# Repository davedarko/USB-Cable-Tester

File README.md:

# USB-Cable-Tester
Test your mini, micro and A-A cables with this little device! 

Infos: https://hackaday.io/project/6858-usb-cable-tester

V0 - OSHPark: https://oshpark.com/shared_projects/k1oxoEwG

V1 coming soon

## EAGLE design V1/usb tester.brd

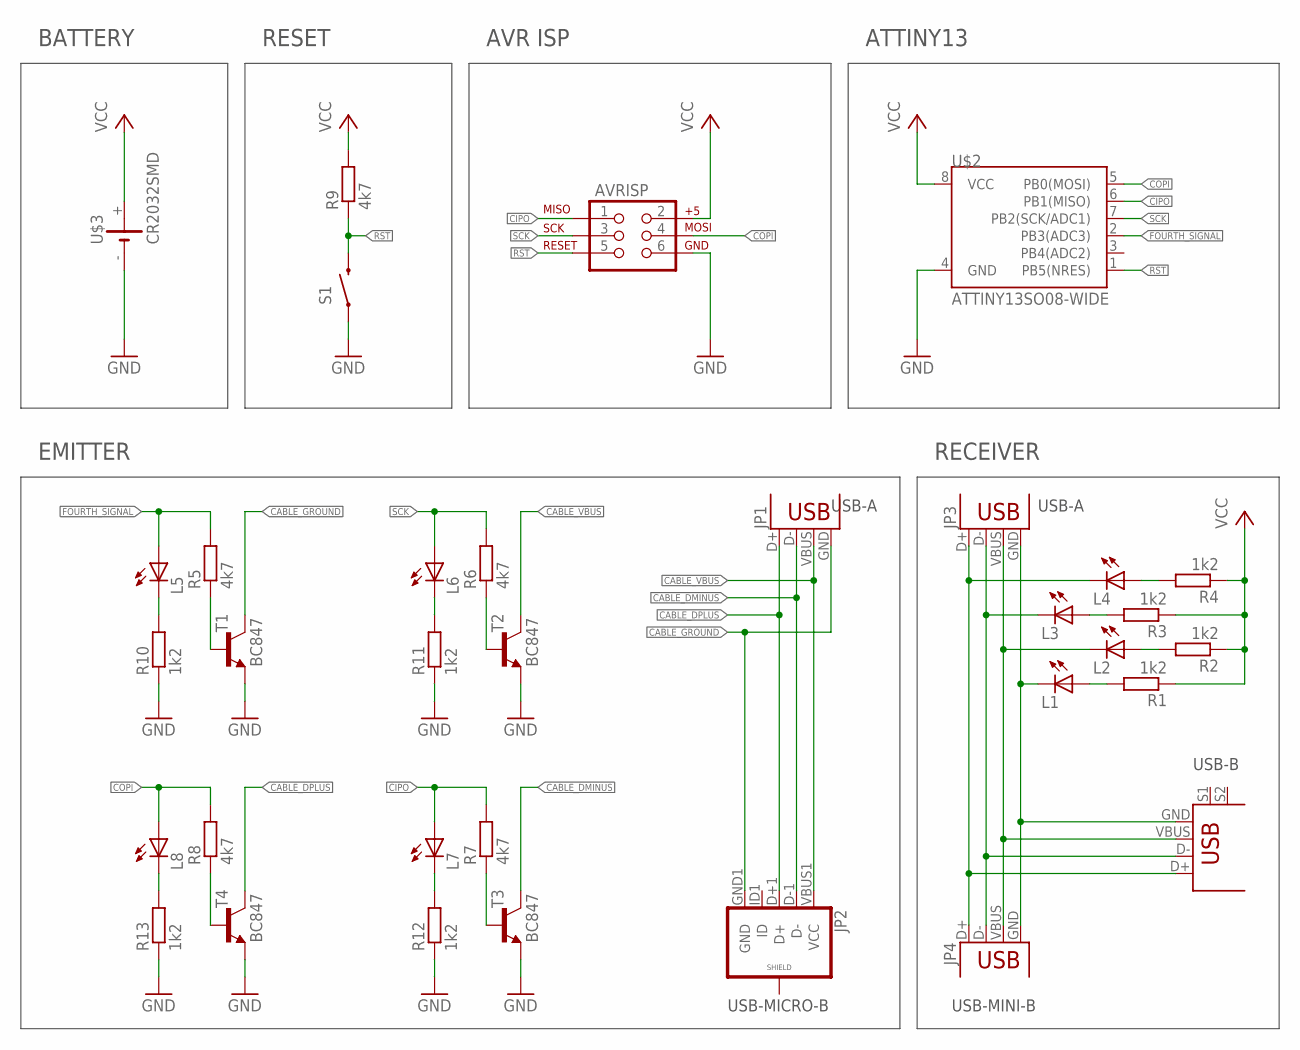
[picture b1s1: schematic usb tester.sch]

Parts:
AVRISP: AVR_SPI_PRG_62X3_LOCK; 2X3_LOCK
JP1, JP3: USB-A-SMD; USB-A-S-NOSILK-FEMALE
JP2: USB_MICROB_PLUG-IDK; USB-AB-MICRO-SMD_SLOT
JP4: USB-SMD-NS; USB-MINIB-NOSTOP
L1, L2, L3, L4, L5, L6, L7, L8: LEDCHIPLED_0805; CHIPLED_0805
R1, R2, R3, R4, R10, R11, R12, R13: 1k2; R0603
R5, R6, R7, R8, R9: 4k7; R0603
S1: SWITCH-MOMENTARY-2SMD-4; TACTILE_SWITCH_TALL
T1, T2, T3, T4: BC847; SOT23
U$1: USB+SHIELD; USB-B-PTH
U$2: ATTINY13SO08-WIDE; SO08-EIAJ
U$3: CR2032SMD

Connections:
CABLE_DMINUS: JP1.D-, JP2.D-1 (D-), T3.3 (C)
CABLE_DPLUS: JP1.D+, JP2.D+1 (D+), T4.3 (C)
CABLE_GROUND: JP1.GND, JP2.GND1 (GND), T1.3 (C)
CABLE_VBUS: JP1.VBUS, JP2.VBUS1 (VCC), T2.3 (C)
CIPO: AVRISP.1, L7.A, R7.2, U$2.6 (PB1(MISO))
COPI: AVRISP.4, L8.A, R8.2, U$2.5 (PB0(MOSI))
FOURTH_SIGNAL: L5.A, R5.2, U$2.2 (PB3(ADC3))
GND: AVRISP.6, R10.1, R11.1, R12.1, R13.1, S1.A2 (1), T1.2 (E), T2.2 (E), T3.2 (E), T4.2 (E), U$2.4 (GND), U$3.-
unnamed: L2.A, R2.2
unnamed: L4.A, R4.2
unnamed: L3.A, R3.2
unnamed: R5.1, T1.1 (B)
unnamed: L1.A, R1.2
unnamed: R7.1, T3.1 (B)
unnamed: R8.1, T4.1 (B)
unnamed: L8.C, R13.2
unnamed: L5.C, R10.2
unnamed: L6.C, R11.2
unnamed: L7.C, R12.2
unnamed: R6.1, T2.1 (B)
OTHER_DMINUS: JP3.D-, JP4.D-, L3.C, U$1.D-
OTHER_DPLUS: JP3.D+, JP4.D+, L4.C, U$1.D+
OTHER_GROUND: JP3.GND, JP4.GND, L1.C, U$1.GND
OTHER_VBUS: JP3.VBUS, JP4.VBUS, L2.C, U$1.VBUS
RST: AVRISP.5, R9.1, S1.B2 (2), U$2.1 (PB5(NRES))
SCK: AVRISP.3, L6.A, R6.2, U$2.7 (PB2(SCK/ADC1))
VCC: AVRISP.2, R1.1, R2.1, R3.1, R4.1, R9.2, U$2.8 (VCC), U$3.+

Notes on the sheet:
RECEIVER
EMITTER
USB-B
USB-A
USB-MICRO-B
USB-MINI-B
BATTERY
RESET
AVR ISP
ATTINY13

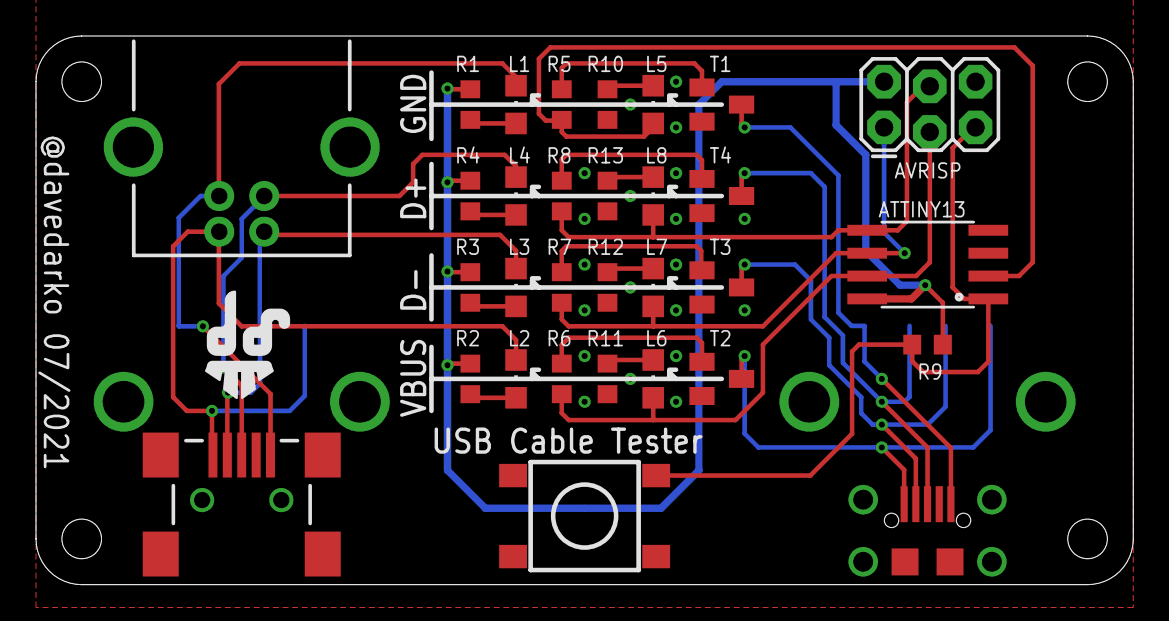
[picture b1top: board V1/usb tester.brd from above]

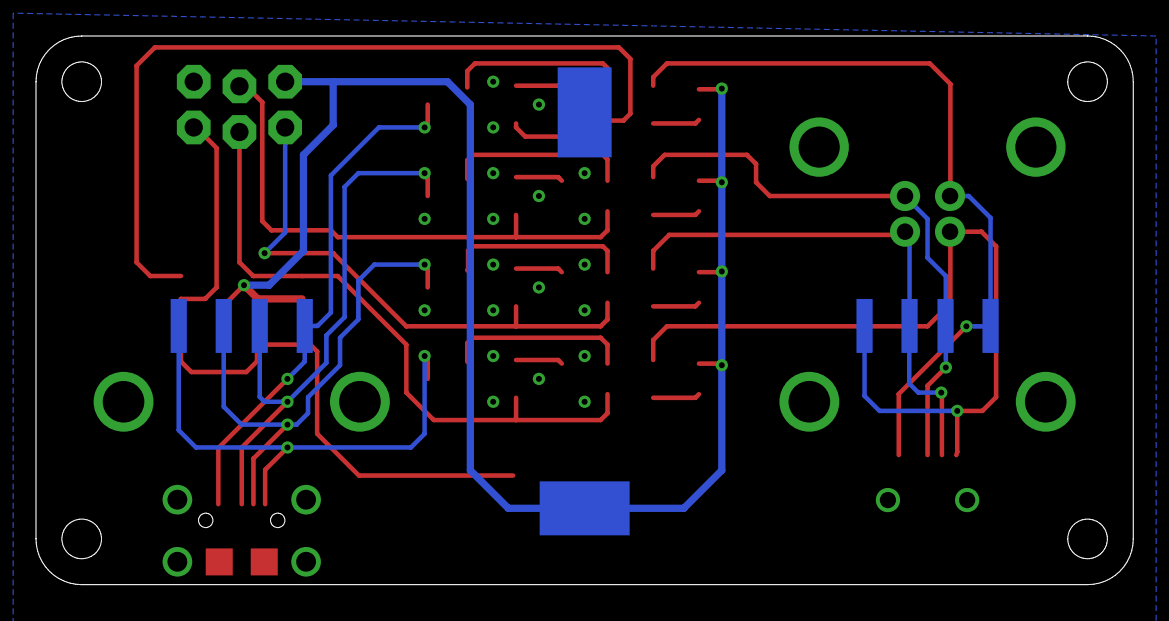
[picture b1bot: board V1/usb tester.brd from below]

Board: 2 copper layers, 61.0 x 30.5 mm, 35 parts (3 on the bottom side), 27 nets.

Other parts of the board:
U$4: DAVEDARKO2_LOGO

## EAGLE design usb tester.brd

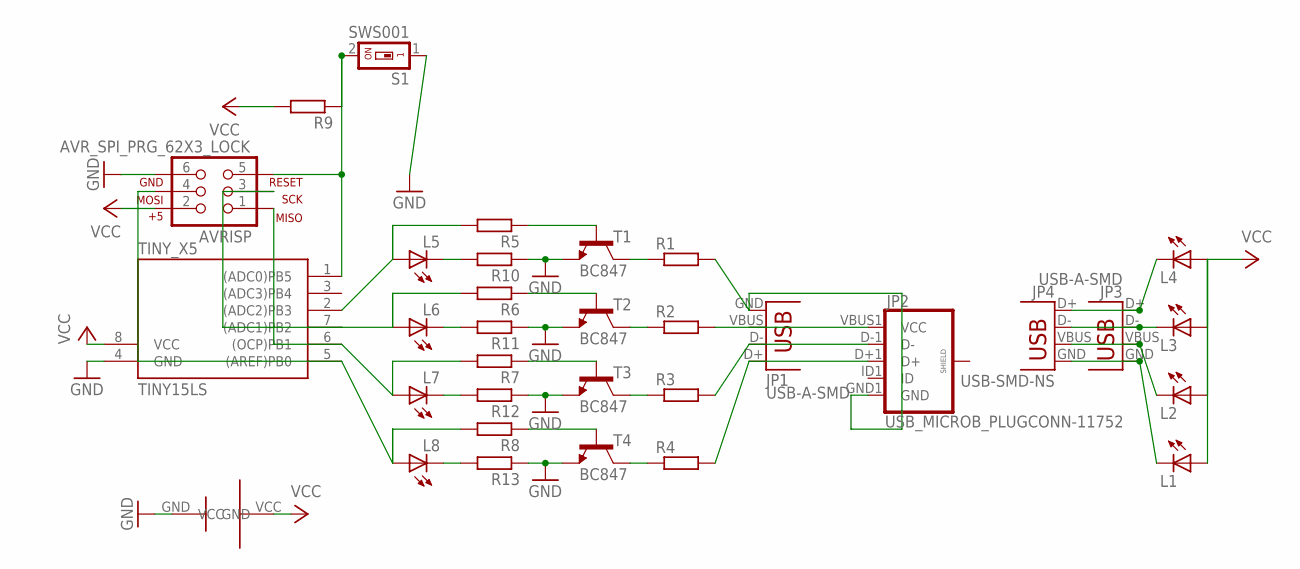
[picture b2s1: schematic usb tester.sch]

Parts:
AVRISP: AVR_SPI_PRG_62X3_LOCK; 2X3_LOCK
JP1, JP3: USB-A-SMD; USB-A-S-NOSILK-FEMALE
JP2: USB_MICROB_PLUGCONN-11752; USB-B-MICRO-SMD_V03
JP4: USB-SMD-NS; USB-MINIB-NOSTOP
L1, L2, L3, L4, L5, L6, L7, L8: LEDSMT1206; 1206
R1, R2, R3, R4, R5, R6, R7, R8, R9, R10, R11, R12, R13: R-EU_R1206; R1206
S1: SWS001; SMS-001
T1, T2, T3, T4: BC847; SOT23
TINY_X5: TINY15LS; SOIC8
U$1: BATTERY

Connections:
GND: AVRISP.6, R10.1, R11.1, R12.1, R13.1, S1.1, T1.2 (E), T2.2 (E), T3.2 (E), T4.2 (E), TINY_X5.4 (GND), U$1.GND
unnamed: R1.1, T1.3 (C)
unnamed: R2.1, T2.3 (C)
unnamed: R3.1, T3.3 (C)
unnamed: R4.1, T4.3 (C)
unnamed: R5.1, T1.1 (B)
unnamed: R7.1, T3.1 (B)
unnamed: AVRISP.1, L7.A, R7.2, TINY_X5.6 ((OCP)PB1)
unnamed: R8.1, T4.1 (B)
unnamed: JP1.GND, JP2.GND1 (GND), R1.2
unnamed: JP1.VBUS, JP2.VBUS1 (VCC), R2.2
unnamed: JP1.D-, JP2.D-1 (D-), R3.2
unnamed: JP1.D+, JP2.D+1 (D+), R4.2
unnamed: AVRISP.4, L8.A, R8.2, TINY_X5.5 ((AREF)PB0)
unnamed: L5.A, R5.2, TINY_X5.2 ((ADC2)PB3)
unnamed: JP3.GND, JP4.GND, L1.C
unnamed: JP3.VBUS, JP4.VBUS, L2.C
unnamed: JP3.D-, JP4.D-, L3.C
unnamed: JP3.D+, JP4.D+, L4.C
unnamed: L8.C, R13.2
unnamed: AVRISP.5, R9.1, S1.2, TINY_X5.1 ((ADC0)PB5)
unnamed: AVRISP.3, L6.A, R6.2, TINY_X5.7 ((ADC1)PB2)
unnamed: L5.C, R10.2
unnamed: L6.C, R11.2
unnamed: L7.C, R12.2
unnamed: R6.1, T2.1 (B)
VCC: AVRISP.2, L1.A, L2.A, L3.A, L4.A, R9.2, TINY_X5.8 (VCC), U$1.VCC

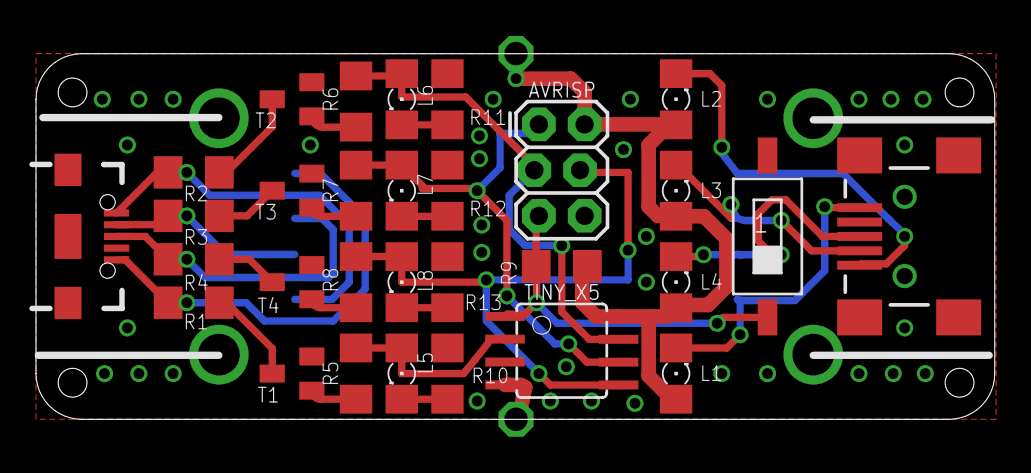
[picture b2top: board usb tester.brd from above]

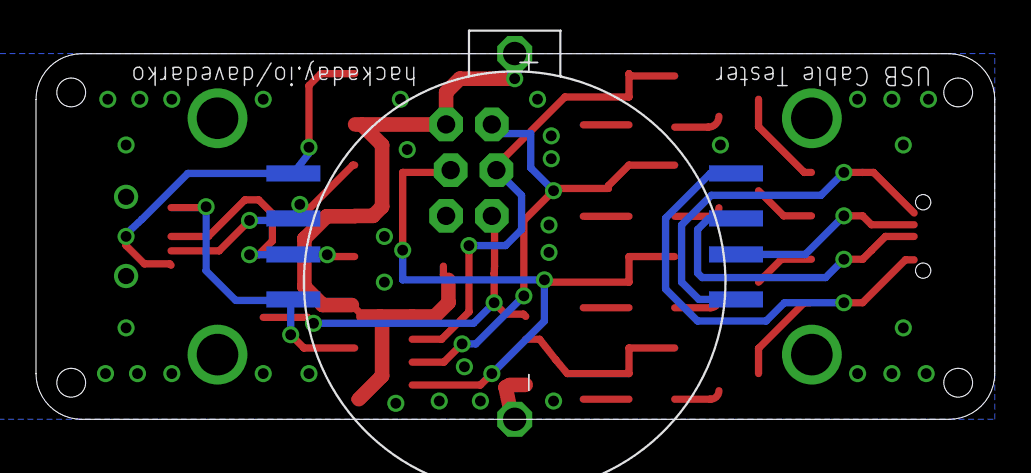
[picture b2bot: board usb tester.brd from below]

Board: 2 copper layers, 53.3 x 20.3 mm, 33 parts (3 on the bottom side), 27 nets.

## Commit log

2015-09-09 Version 1.0
2017-01-06 Arduino Code
2017-01-06 library for battery
2021-07-18 2021 revision, new layout
2021-08-14 values

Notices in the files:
parts and their libraries:
SparkFun-Connectors: Licensing: Creative Commons ShareAlike 4.0 International - https://creativecommons.org/licenses/by-sa/4.0
